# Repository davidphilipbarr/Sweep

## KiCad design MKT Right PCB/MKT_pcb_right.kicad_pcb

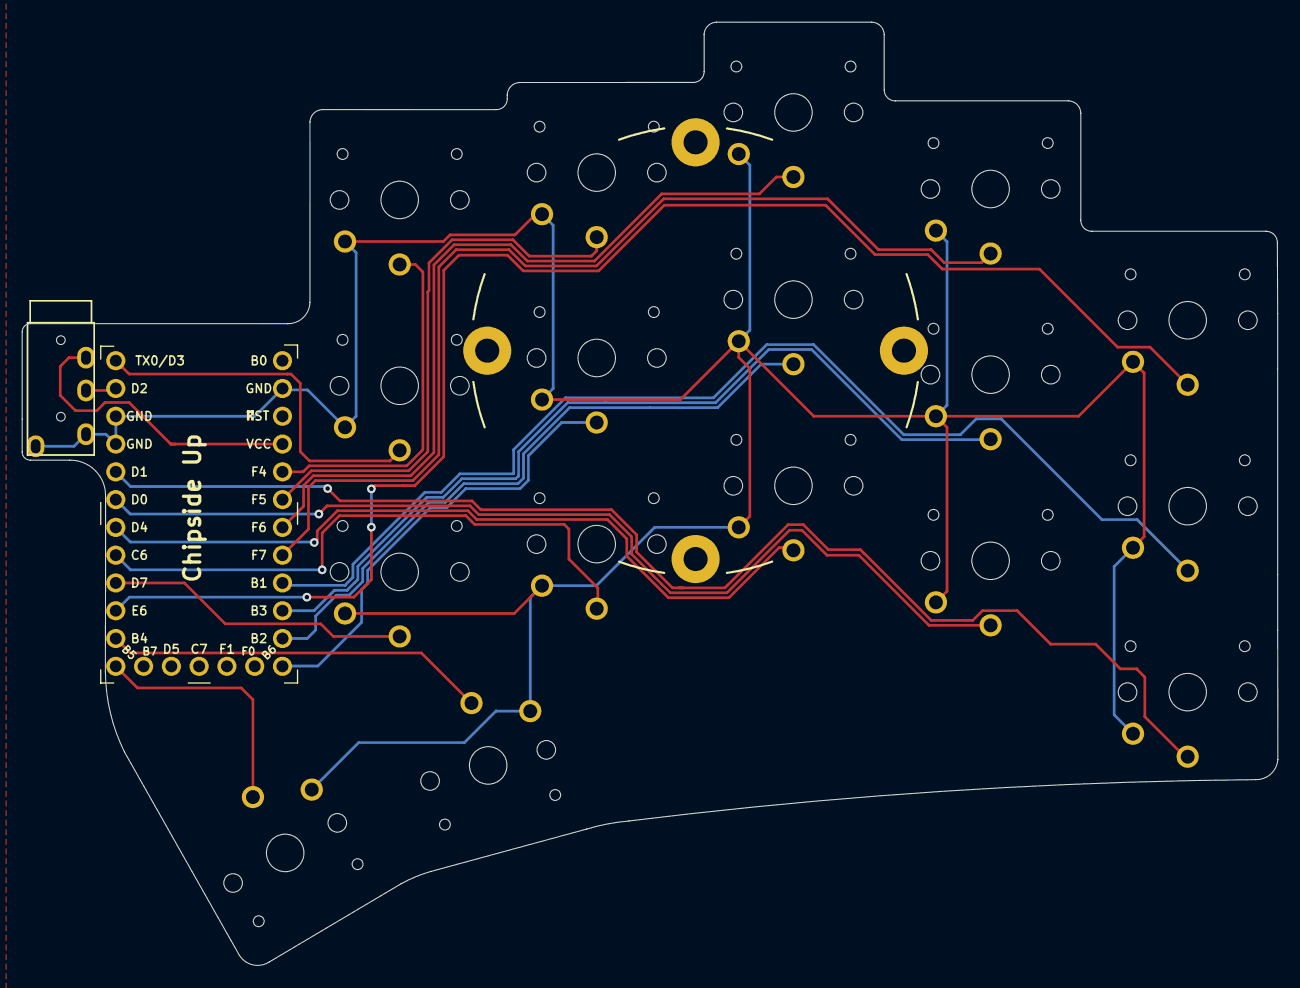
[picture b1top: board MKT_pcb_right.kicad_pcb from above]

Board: 2 copper layers, 114.8 x 86.2 mm, 19 parts (0 on the bottom side), 20 nets.

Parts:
J1: AudioJack4dpb; TRRS-PJ-320A
SW2_r1, SW3_r1, SW4_r1, SW5_r1, SW6_r1, SW7_r1, SW8_r1, SW9_r1, SW11_r1, SW12_r1, SW13_r1, SW15_r1, SW16_r1, SW17_r1, SW18_r1, SW20_r1, SW21_r1: SW_Push; SW_PG1350_nonrev_DPB
U1: Elite-C-29pin-holes

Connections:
Switch1_r: SW2_r1.1, U1.10
Switch2_r: SW3_r1.1, U1.17
Switch3_r: SW4_r1.1, U1.18
Switch4_r: SW5_r1.1, U1.19
Switch5_r: SW6_r1.1, U1.20
Switch6_r: SW7_r1.1, U1.16
Switch7_r: SW8_r1.1, U1.15
Switch8_r: SW9_r1.1, U1.14
Switch9_r: SW11_r1.1, U1.13
Switch10_r: SW12_r1.1, U1.1
Switch11_r: SW13_r1.1, U1.5
Switch12_r: SW18_r1.1, U1.6
Switch13_r: SW15_r1.1, U1.7
Switch14_r: SW16_r1.1, U1.8
Switch15_r: SW17_r1.1, U1.9
Switch16_r: SW21_r1.1, U1.11
Switch17_r: SW20_r1.1, U1.12
Switch18_r: J1.R1, U1.2
gnd: J1.S, J1.T, SW2_r1.2, SW3_r1.2, SW4_r1.2, SW5_r1.2, SW6_r1.2, SW7_r1.2, SW8_r1.2, SW9_r1.2, SW11_r1.2, SW12_r1.2, SW13_r1.2, SW15_r1.2, SW16_r1.2, SW17_r1.2, SW18_r1.2, SW20_r1.2, SW21_r1.2, U1.3, U1.4, U1.23
vcc: J1.R2, U1.21

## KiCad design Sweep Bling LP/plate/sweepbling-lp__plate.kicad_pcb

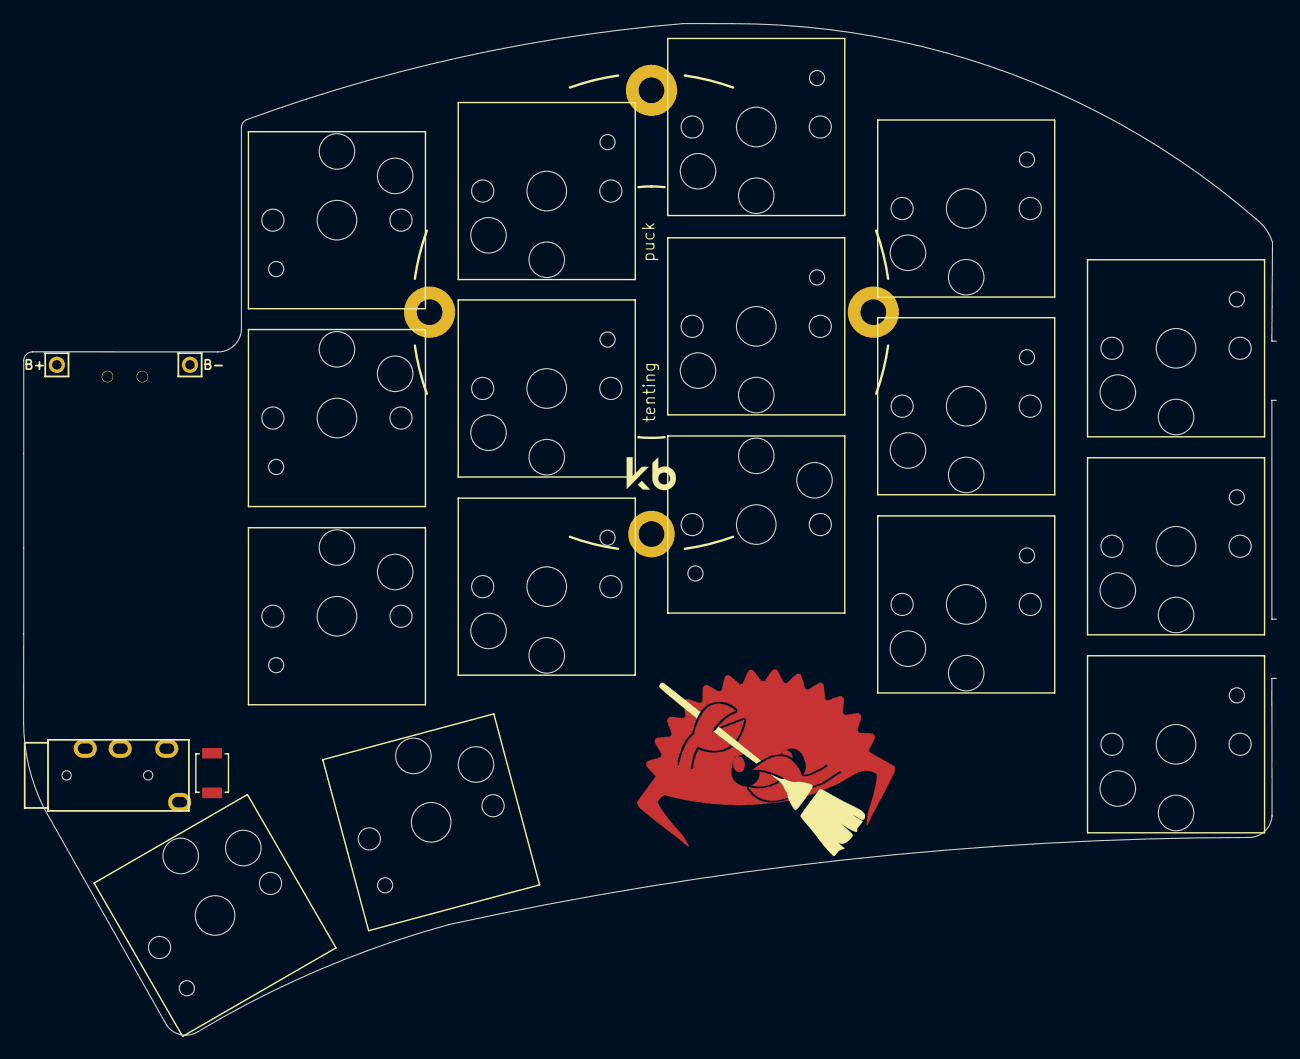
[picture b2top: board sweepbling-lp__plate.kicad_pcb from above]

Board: 2 copper layers, 107.6 x 86.9 mm, 23 parts (1 on the bottom side), 2 nets, no tracks yet.

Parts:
B+: MountingHole_Pad; 1pin_conn
B-: MountingHole_Pad; 1pin_conn
J1: AudioJack4dpb; TRRS-PJ-320A
POWER SW: SW_SPDT; SPDT_C128955
REF_PUCK_R: Tenting Puck; Tenting_Puck2
RSW2: SW_Push; SW_SPST_B3U-1000P
SW2_r1, SW3_r1, SW4_r1, SW5_r1, SW6_r1, SW7_r1, SW8_r1, SW9_r1, SW11_r1, SW12_r1, SW13_r1, SW15_r1, SW16_r1, SW17_r1, SW18_r1, SW20_r1, SW21_r1: SW_Push; SW_Hotswap_Kailh_Choc_V1_no_bounds

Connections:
BT+: B+.1, POWER SW.2
gnd: B-.1, J1.S, J1.T, RSW2.1, SW2_r1.2, SW3_r1.2, SW4_r1.2, SW5_r1.2, SW6_r1.2, SW7_r1.2, SW8_r1.2, SW9_r1.2, SW11_r1.2, SW12_r1.2, SW13_r1.2, SW15_r1.2, SW16_r1.2, SW17_r1.2, SW18_r1.2, SW20_r1.2, SW21_r1.2

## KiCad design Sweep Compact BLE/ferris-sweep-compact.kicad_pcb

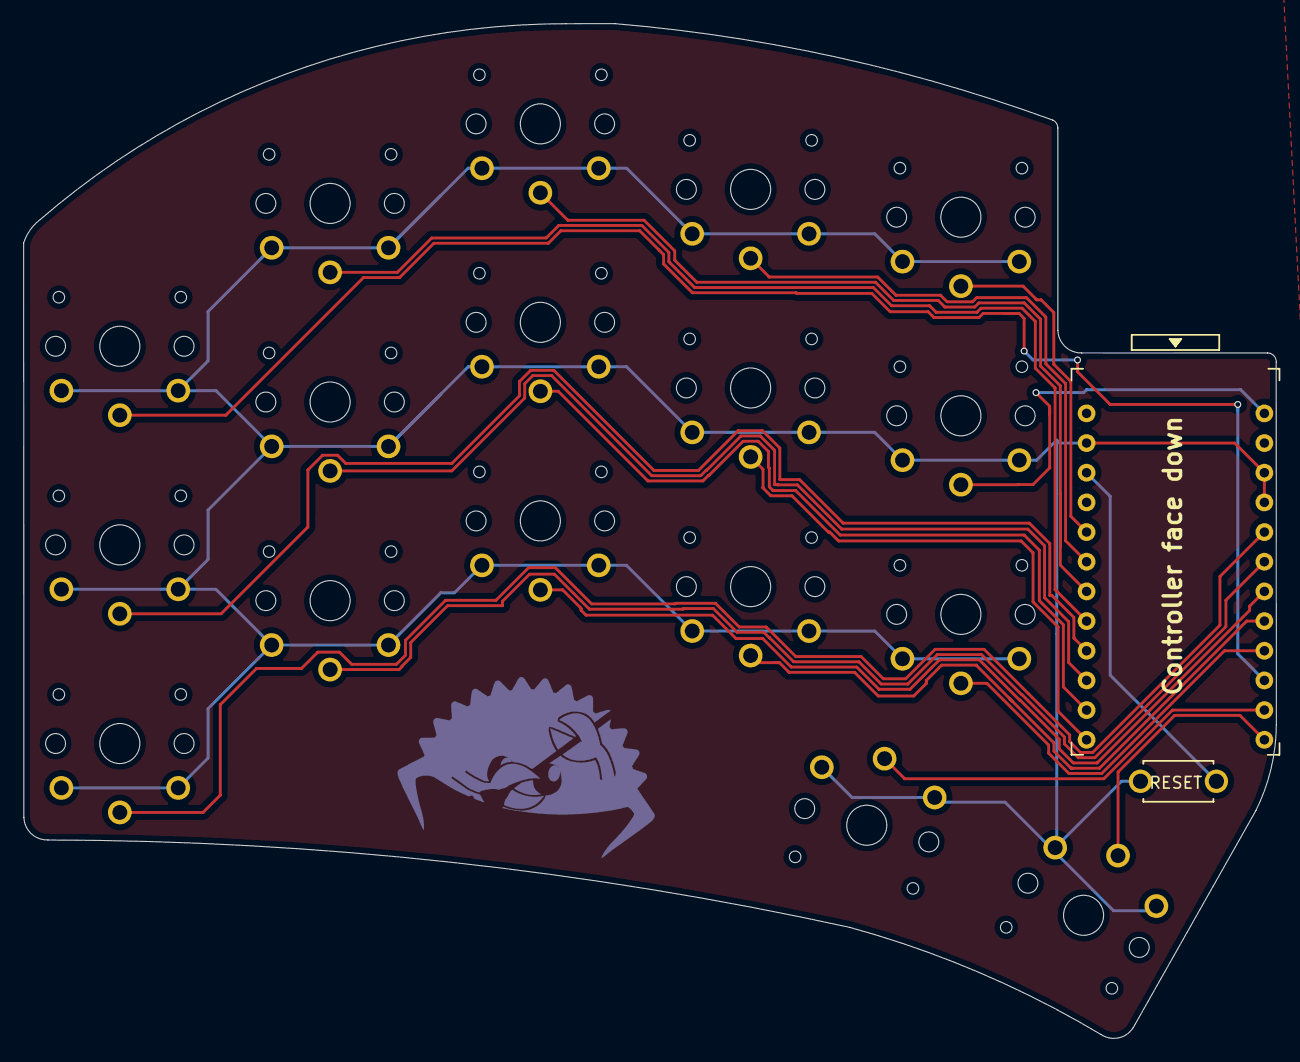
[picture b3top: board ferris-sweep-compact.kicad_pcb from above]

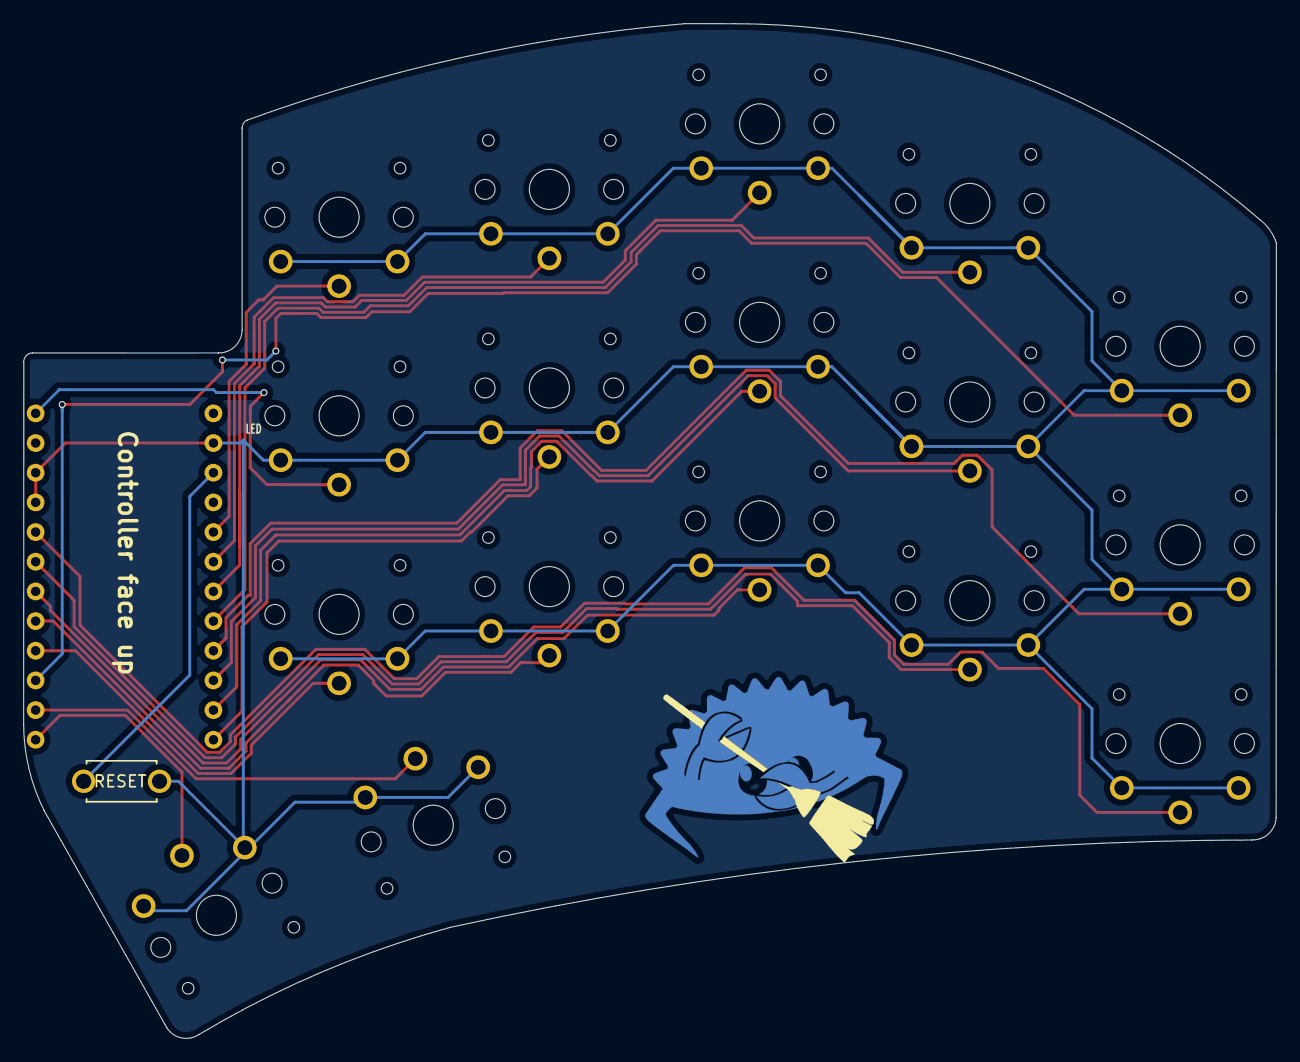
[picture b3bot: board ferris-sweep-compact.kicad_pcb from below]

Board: 2 copper layers, 107.2 x 86.9 mm, 19 parts (2 on the bottom side), 19 nets.

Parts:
RSW1: Val**; ResetSW
SW2, SW3, SW4, SW5, SW6, SW8, SW9, SW10, SW11, SW12, SW14, SW15, SW16, SW17, SW18, SW20, SW21: SW_PUSH; SW_PG1350_reversible_b2
U1: ProMicro; ProMicro_v3

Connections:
GND: RSW1.2, SW2.2, SW3.2, SW4.2, SW5.2, SW6.2, SW8.2, SW9.2, SW10.2, SW11.2, SW12.2, SW14.2, SW15.2, SW16.2, SW17.2, SW18.2, SW20.2, SW21.2, U1.3, U1.4, U1.23
LED: SW12.1, U1.1
unnamed: SW20.1, U1.11
unnamed: SW21.1, U1.12
unnamed: SW11.1, U1.13
unnamed: SW10.1, U1.14
SCL: SW15.1, U1.6
SDA: SW14.1, U1.5
col0: SW6.1, U1.20
col1: SW5.1, U1.19
col2: SW4.1, U1.18
col3: SW3.1, U1.17
col4: SW8.1, U1.16
col5: SW9.1, U1.15
reset: RSW1.1, U1.22
row0: SW16.1, U1.7
row1: SW17.1, U1.8
row2: SW18.1, U1.9
row3: SW2.1, U1.10
